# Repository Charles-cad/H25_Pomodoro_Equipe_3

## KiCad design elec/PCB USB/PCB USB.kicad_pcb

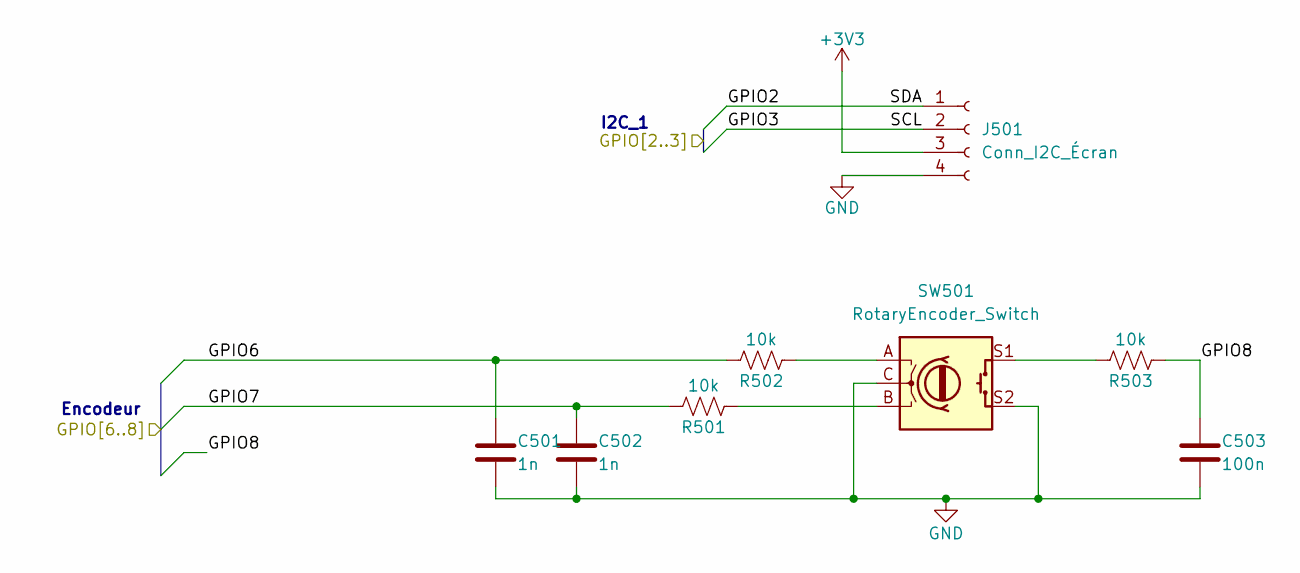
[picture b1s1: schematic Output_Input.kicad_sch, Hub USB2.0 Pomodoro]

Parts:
C501, C502: 1n; C_0603_1608Metric
C503: 100n; C_0603_1608Metric
J501: Conn_I2C_Écran; PinSocket_1x04_P2.54mm_Vertical
R501, R502, R503: 10k; R_0603_1608Metric
SW501: RotaryEncoder_Switch; RotaryEncoder_Bourns_Horizontal_PEC12R-2x17F-Sxxxx

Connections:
/MCU/GPIO6: C501.1, R502.1; also elsewhere on the board
/MCU/GPIO7: C502.1, R501.1; also elsewhere on the board
/MCU/GPIO8: C503.1, R503.2; also elsewhere on the board
unnamed: R501.2, SW501.B
unnamed: R502.2, SW501.A
unnamed: R503.1, SW501.S1

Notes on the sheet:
I2C_1
Encodeur

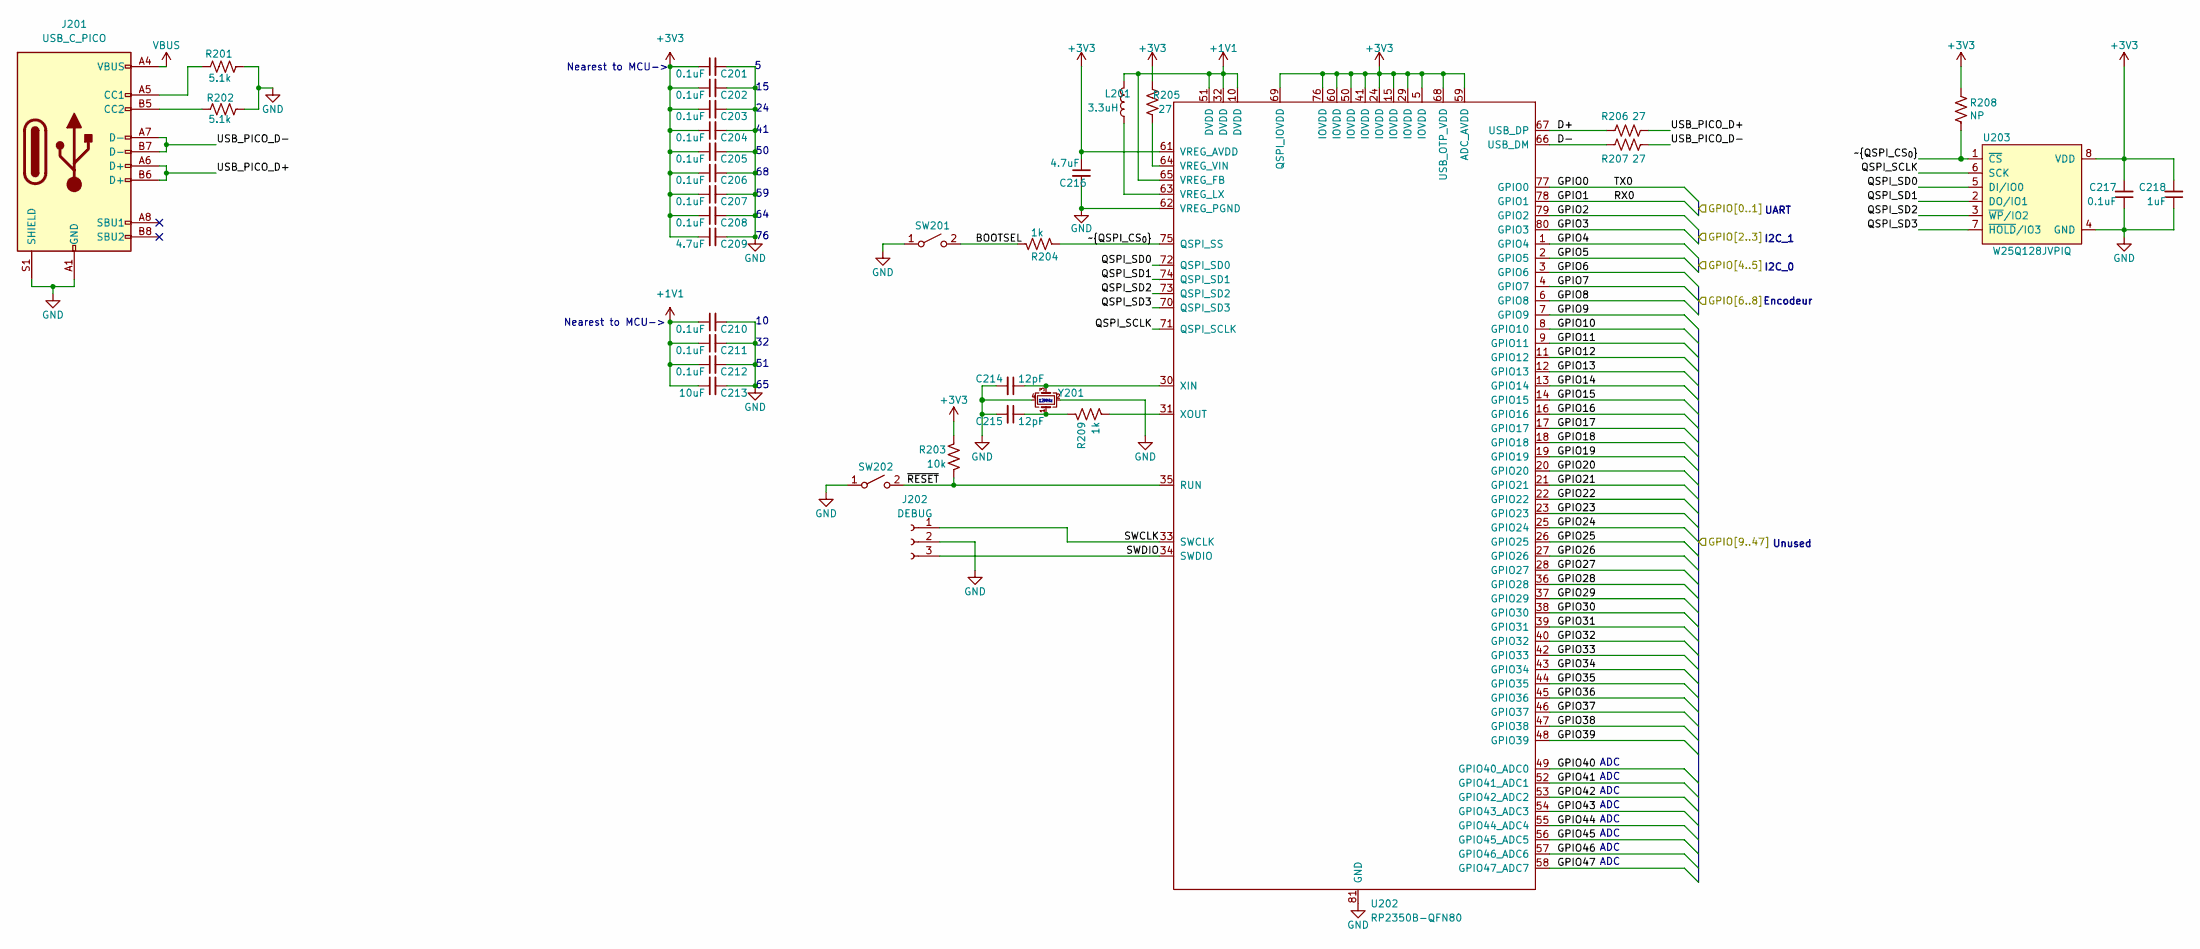
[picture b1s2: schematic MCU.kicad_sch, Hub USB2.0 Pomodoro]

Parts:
C201, C202, C203, C204, C205, C206, C207, C208, C210, C211, C212, C217: 0.1uF; C_0603_1608Metric
C209, C216: 4.7uF; C_0805_2012Metric
C213: 10uF; C_0805_2012Metric
C214, C215: 12pF; C_0603_1608Metric
C218: 1uF; C_0603_1608Metric
J201: USB_C_PICO; USB_C_Receptacle_G-Switch_GT-USB-7010ASV
J202: DEBUG; PinHeader_1x03_P2.54mm_Vertical
L201: 3.3uH; R_0805_2012Metric
R201, R202: 5.1k; R_0603_1608Metric_Pad0.98x0.95mm_HandSolder
R203: 10k; R_0603_1608Metric
R204, R209: 1k; R_0603_1608Metric
R205, R206, R207: 27; R_0603_1608Metric
R208: NP; R_0603_1608Metric
SW201: SW_BOOTSEL; SW_SPST_B3U-1000P; LCSC C561514
SW202: SW_RESET; SW_SPST_B3U-1000P; LCSC C561514
U202: RP2350B-QFN80; QFN-80-1EP_10x10mm_P0.4mm_EP3.4x3.4mm_ThermalVias
U203: W25Q128JVPIQ; WSON-8-1EP_6x5mm_P1.27mm_EP3.4x4mm; LCSC C190862
Y201: CM4012M00012001; Crystal_SMD_2520-4Pin_2.5x2.0mm; LCSC C7294611

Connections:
+1V1: C210.1, C211.1, C212.1, C213.1, L201.2, U202.10 (DVDD), U202.32 (DVDD), U202.51 (DVDD), U202.65 (VREG_FB)
+3V3: C201.1, C202.1, C203.1, C204.1, C205.1, C206.1, C207.1, C208.1, C209.1, C216.1, C217.2, C218.2, R203.1, R205.1, R208.2, U202.5 (IOVDD), U202.15 (IOVDD), U202.24 (IOVDD), U202.29 (IOVDD), U202.41 (IOVDD), U202.50 (IOVDD), U202.59 (ADC_AVDD), U202.60 (IOVDD), U202.61 (VREG_AVDD), U202.68 (USB_OTP_VDD), U202.69 (QSPI_IOVDD), U202.76 (IOVDD), U203.8 (VDD); also elsewhere on the board
/MCU/BOOTSEL: R204.2, SW201.2 (B)
/MCU/D+: R206.1, U202.67 (USB_DP)
/MCU/D-: R207.2, U202.66 (USB_DM)
/MCU/GPIO0: U202.77 (GPIO0)
/MCU/GPIO1: U202.78 (GPIO1)
/MCU/GPIO2: U202.79 (GPIO2); also elsewhere on the board
/MCU/GPIO3: U202.80 (GPIO3); also elsewhere on the board
/MCU/GPIO4: U202.1 (GPIO4)
/MCU/GPIO5: U202.2 (GPIO5)
/MCU/GPIO6: U202.3 (GPIO6); also elsewhere on the board
/MCU/GPIO7: U202.4 (GPIO7); also elsewhere on the board
/MCU/GPIO8: U202.6 (GPIO8); also elsewhere on the board
/MCU/GPIO9: U202.7 (GPIO9)
/MCU/GPIO10: U202.8 (GPIO10)
/MCU/GPIO11: U202.9 (GPIO11)
/MCU/GPIO12: U202.11 (GPIO12)
/MCU/GPIO13: U202.12 (GPIO13)
/MCU/GPIO14: U202.13 (GPIO14)
/MCU/GPIO15: U202.14 (GPIO15)
/MCU/GPIO16: U202.16 (GPIO16)
/MCU/GPIO17: U202.17 (GPIO17)
/MCU/GPIO18: U202.18 (GPIO18)
/MCU/GPIO19: U202.19 (GPIO19)
/MCU/GPIO20: U202.20 (GPIO20)
/MCU/GPIO21: U202.21 (GPIO21)
/MCU/GPIO22: U202.22 (GPIO22)
/MCU/GPIO23: U202.23 (GPIO23)
/MCU/GPIO24: U202.25 (GPIO24)
/MCU/GPIO25: U202.26 (GPIO25)
/MCU/GPIO26: U202.27 (GPIO26)
/MCU/GPIO27: U202.28 (GPIO27)
/MCU/GPIO28: U202.36 (GPIO28)
/MCU/GPIO29: U202.37 (GPIO29)
/MCU/GPIO30: U202.38 (GPIO30)
/MCU/GPIO31: U202.39 (GPIO31)
/MCU/GPIO32: U202.40 (GPIO32)
/MCU/GPIO33: U202.42 (GPIO33)
/MCU/GPIO34: U202.43 (GPIO34)
/MCU/GPIO35: U202.44 (GPIO35)
/MCU/GPIO36: U202.45 (GPIO36)
/MCU/GPIO37: U202.46 (GPIO37)
/MCU/GPIO38: U202.47 (GPIO38)
/MCU/GPIO39: U202.48 (GPIO39)
/MCU/GPIO40: U202.49 (GPIO40_ADC0)
/MCU/GPIO41: U202.52 (GPIO41_ADC1)
/MCU/GPIO42: U202.53 (GPIO42_ADC2)
/MCU/GPIO43: U202.54 (GPIO43_ADC3)
/MCU/GPIO44: U202.55 (GPIO44_ADC4)
/MCU/GPIO45: U202.56 (GPIO45_ADC5)
/MCU/GPIO46: U202.57 (GPIO46_ADC6)
/MCU/GPIO47: U202.58 (GPIO47_ADC7)
/MCU/QSPI_SCLK: U202.71 (QSPI_SCLK), U203.6 (SCK)
/MCU/QSPI_SD0: U202.72 (QSPI_SD0), U203.5 (DI/IO0)
/MCU/QSPI_SD1: U202.74 (QSPI_SD1), U203.2 (DO/IO1)
/MCU/QSPI_SD2: U202.73 (QSPI_SD2), U203.3 (~WP/IO2)
/MCU/QSPI_SD3: U202.70 (QSPI_SD3), U203.7 (~HOLD/IO3)
/MCU/SWCLK: J202.1, U202.33 (SWCLK); also elsewhere on the board
/MCU/SWDIO: J202.3, U202.34 (SWDIO); also elsewhere on the board
/MCU/USB_PICO_D+: J201.A6 (D+), J201.B6 (D+), R206.2
/MCU/USB_PICO_D-: J201.A7 (D-), J201.B7 (D-), R207.1
/MCU/~QSPI_CS_{0}: R204.1, R208.1, U202.75 (QSPI_SS), U203.1 (~CS)
/MCU/~RESET: R203.2, SW202.2 (B), U202.35 (RUN)
unnamed: C215.1, R209.1, Y201.1
unnamed: J201.A5 (CC1), R201.1
unnamed: J201.B5 (CC2), R202.1
unnamed: L201.1, U202.63 (VREG_LX)
unnamed: R205.2, U202.64 (VREG_VIN)
unnamed: C214.1, U202.30 (XIN), Y201.3
unnamed: R209.2, U202.31 (XOUT)
VBUS: J201.A4 (VBUS), J201.A9 (VBUS), J201.B4 (VBUS), J201.B9 (VBUS); also elsewhere on the board

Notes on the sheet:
Encodeur
Nearest to MCU->
UART
I2C_0
ADC
I2C_1
12MHz
Unused

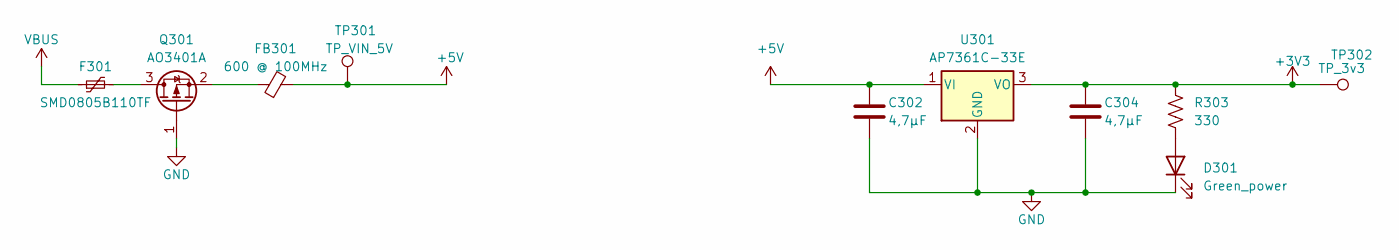
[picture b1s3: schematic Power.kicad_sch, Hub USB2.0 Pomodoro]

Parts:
C302, C304: 4,7µF; C_0805_2012Metric_Pad1.18x1.45mm_HandSolder
D301: Green_power; D_0805_2012Metric
F301: SMD0805B110TF; Fuse_0805_2012Metric
FB301: 600 @ 100MHz; R_0805_2012Metric_Pad1.20x1.40mm_HandSolder
Q301: AO3401A; SOT-23
R303: 330; R_0603_1608Metric_Pad0.98x0.95mm_HandSolder
TP301: TP_VIN_5V; TestPoint_Pad_D1.0mm
TP302: TP_3v3; TestPoint_Pad_D1.0mm
U301: AP7361C-33E; SOT-223-3_TabPin2

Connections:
+3V3: C304.2, R303.1, TP302.1, U301.3 (VO); also elsewhere on the board
+5V: C302.2, FB301.2, TP301.1, U301.1 (VI); also elsewhere on the board
unnamed: D301.2 (A), R303.2
unnamed: F301.2, Q301.3 (D)
unnamed: FB301.1, Q301.2 (S)
VBUS: F301.1; also elsewhere on the board

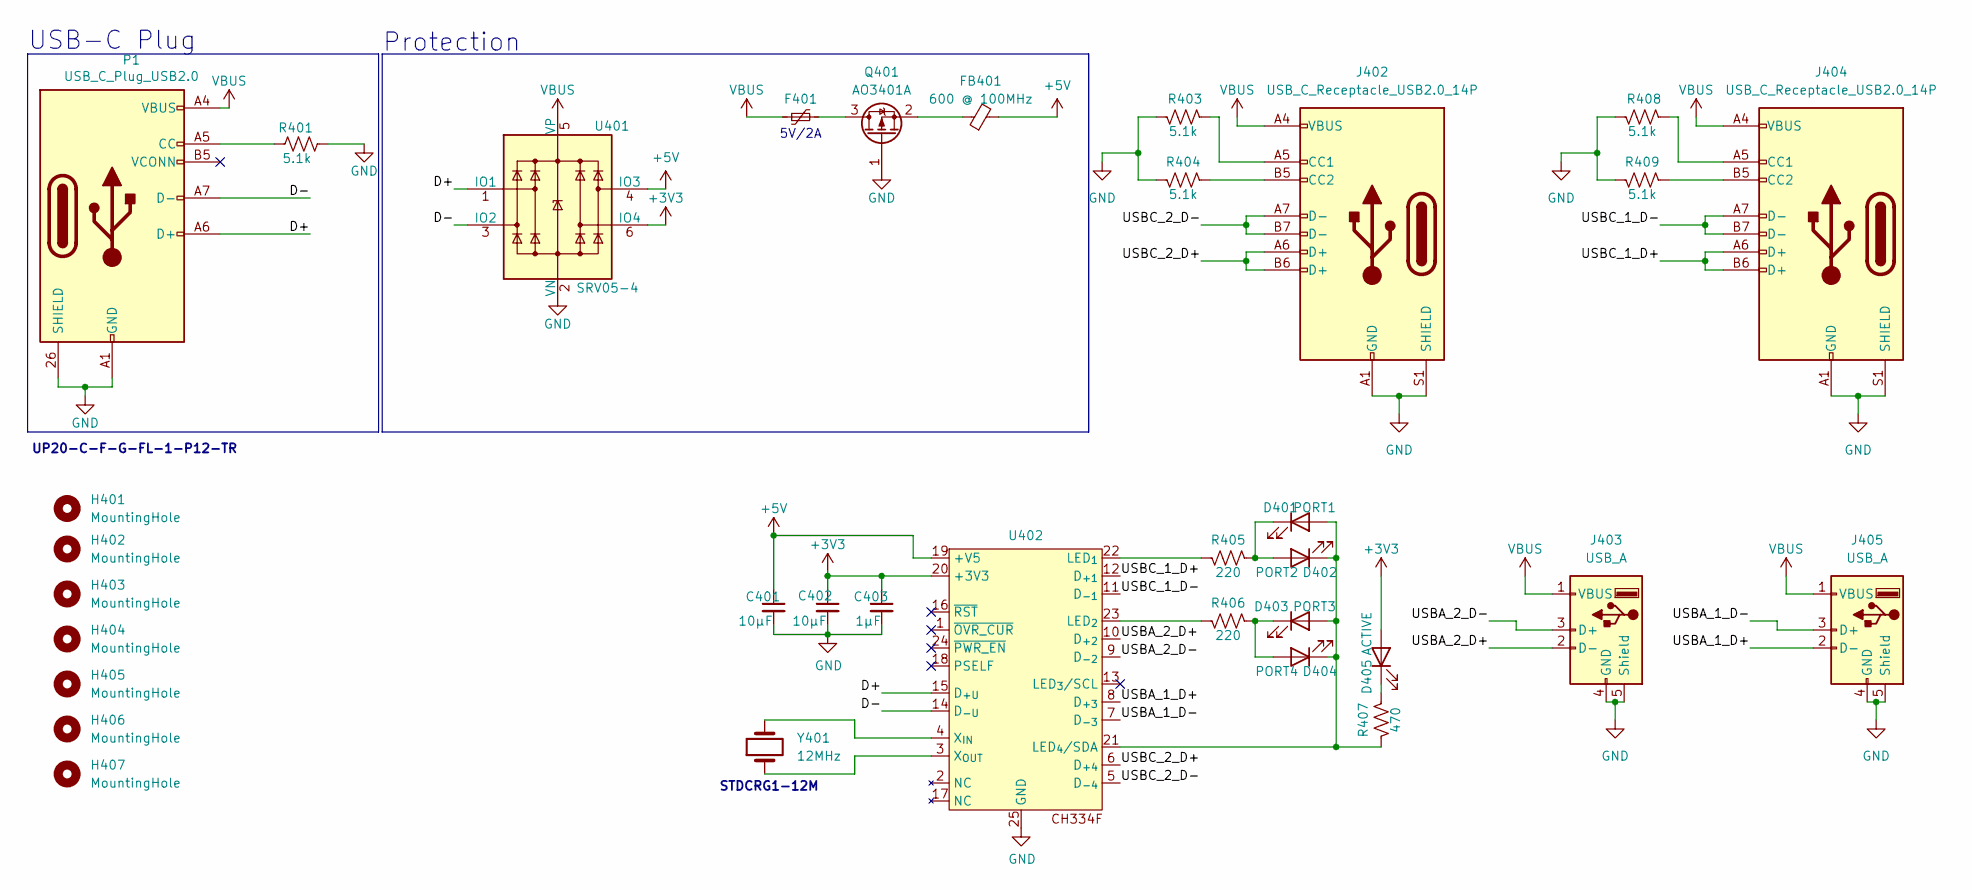
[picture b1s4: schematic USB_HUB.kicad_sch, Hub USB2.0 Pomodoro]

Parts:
C401, C402: 10µF; C_0805_2012Metric
C403: 1µF; C_0603_1608Metric
D401: PORT1; D_0805_2012Metric
D402: PORT2; D_0805_2012Metric
D403: PORT3; D_0805_2012Metric
D404: PORT4; D_0805_2012Metric
D405: ACTIVE; D_0805_2012Metric
F401: SMD0805B110TF; Fuse_0805_2012Metric
FB401: 600 @ 100MHz; R_0805_2012Metric_Pad1.20x1.40mm_HandSolder
H401, H402, H403, H404, H405, H406, H407: MountingHole; MountingHole_2.2mm_M2
J402, J404: USB_C_Receptacle_USB2.0_14P; USB_C_Receptacle_G-Switch_GT-USB-7010ASV
J403, J405: USB_A; USB_A_CONNFLY_DS1095-WNR0
P1: USB_C_Plug_USB2.0; UP20-C-F-G-FL-1-P12-TR; MPN C2856663
Q401: AO3401A; SOT-23
R401: 5.1k; R_0603_1608Metric_Pad0.98x0.95mm_HandSolder
R403, R404, R408, R409: 5.1k; R_0603_1608Metric
R405, R406: 220; R_0603_1608Metric
R407: 470; R_0603_1608Metric
U401: SRV05-4; SOT-23-6
U402: HVQFN-24-1EP_4x4mm_P0.5mm_EP2.6x2.6mm
Y401: 12MHz; Crystal_SMD_3225-4Pin_3.2x2.5mm

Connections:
+3V3: C402.1, C403.1, D405.2 (A), U401.6 (IO4), U402.20 (+3V3); also elsewhere on the board
+5V: C401.1, FB401.2, U401.4 (IO3), U402.19 (+V5); also elsewhere on the board
/USB_HUB/D+: P1.A6 (D+), U401.1 (IO1), U402.15 (D_{+U})
/USB_HUB/D-: P1.A7 (D-), U401.3 (IO2), U402.14 (D_{-U})
/USB_HUB/USBA_1_D+: J405.2 (D-), U402.8 (D_{+3})
/USB_HUB/USBA_1_D-: J405.3 (D+), U402.7 (D_{-3})
/USB_HUB/USBA_2_D+: J403.2 (D-), U402.10 (D_{+2})
/USB_HUB/USBA_2_D-: J403.3 (D+), U402.9 (D_{-2})
/USB_HUB/USBC_1_D+: J404.A6 (D+), J404.B6 (D+), U402.12 (D_{+1})
/USB_HUB/USBC_1_D-: J404.A7 (D-), J404.B7 (D-), U402.11 (D_{-1})
/USB_HUB/USBC_2_D+: J402.A6 (D+), J402.B6 (D+), U402.6 (D_{+4})
/USB_HUB/USBC_2_D-: J402.A7 (D-), J402.B7 (D-), U402.5 (D_{-4})
unnamed: D401.2 (A), D402.1 (K), D403.2 (A), D404.1 (K), R407.2, U402.21 (LED_{4}/SDA)
unnamed: D401.1 (K), D402.2 (A), R405.1
unnamed: D403.1 (K), D404.2 (A), R406.1
unnamed: D405.1 (K), R407.1
unnamed: J402.A5 (CC1), R403.1
unnamed: J402.B5 (CC2), R404.1
unnamed: J404.A5 (CC1), R408.1
unnamed: J404.B5 (CC2), R409.1
unnamed: P1.A5 (CC), R401.1
unnamed: F401.2, Q401.3 (D)
unnamed: FB401.1, Q401.2 (S)
unnamed: R405.2, U402.22 (LED_{1})
unnamed: R406.2, U402.23 (LED_{2})
unnamed: U402.3 (X_{OUT}), Y401.1
VBUS: F401.1, J402.A4 (VBUS), J402.A9 (VBUS), J402.B4 (VBUS), J402.B9 (VBUS), J403.1 (VBUS), J404.A4 (VBUS), J404.A9 (VBUS), J404.B4 (VBUS), J404.B9 (VBUS), J405.1 (VBUS), P1.A4 (VBUS), P1.A9 (VBUS), P1.B4 (VBUS), P1.B9 (VBUS), U401.5 (VP); also elsewhere on the board

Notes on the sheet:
STDCRG1-12M
Protection
UP20-C-F-G-FL-1-P12-TR
5V/2A
USB-C Plug

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
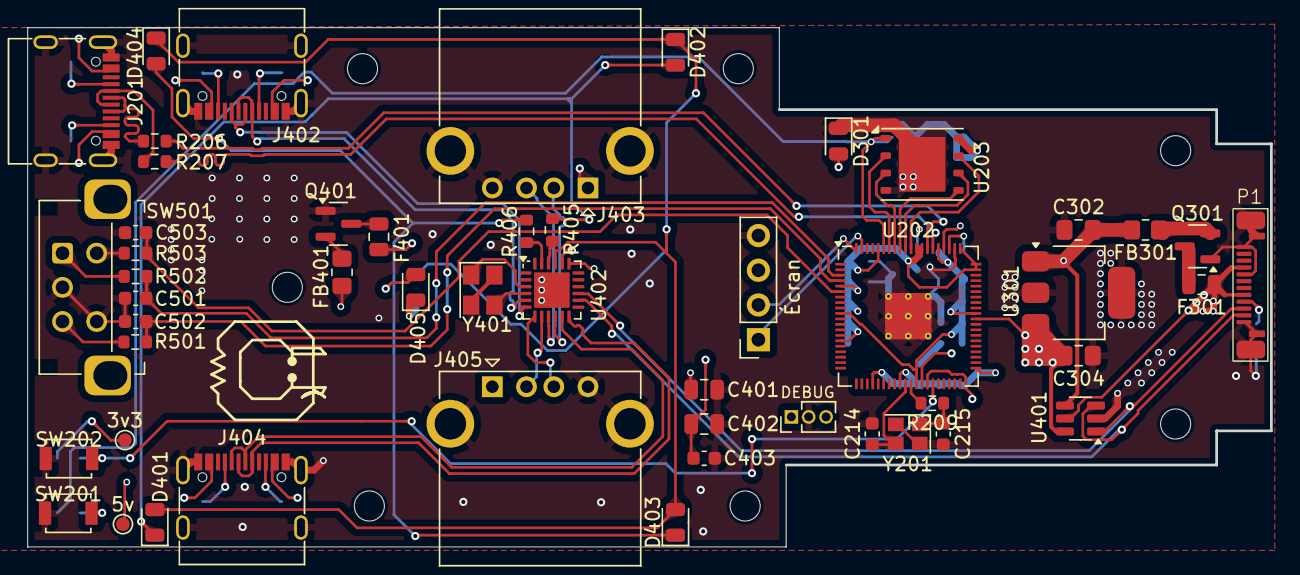
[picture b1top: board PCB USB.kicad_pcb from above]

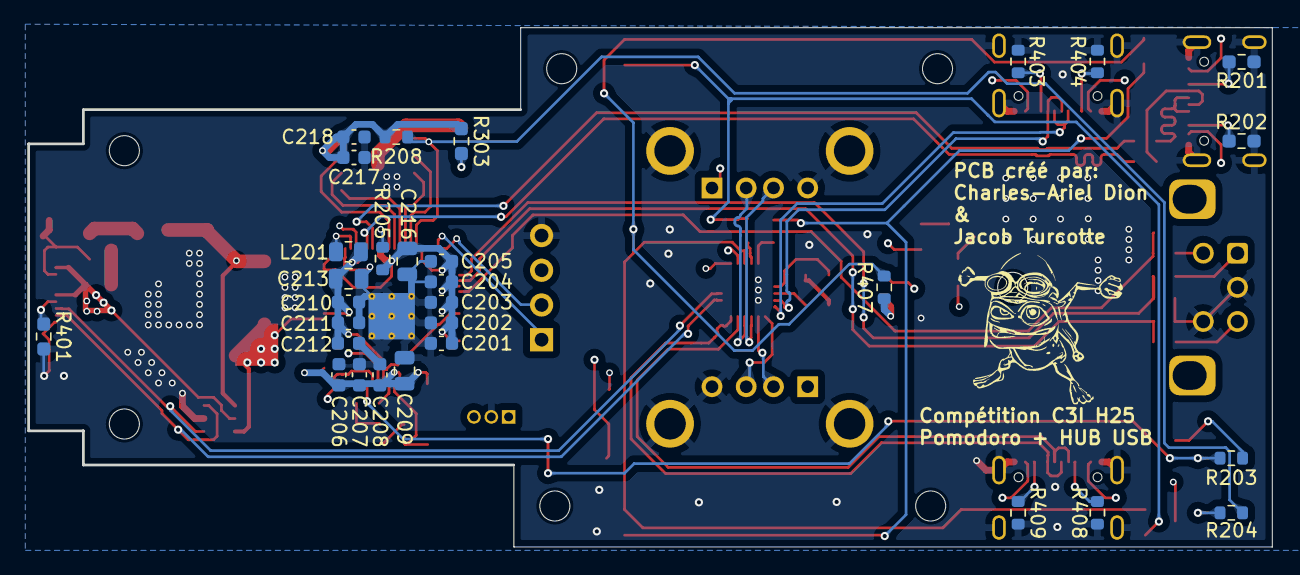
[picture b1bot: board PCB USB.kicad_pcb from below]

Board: 4 copper layers, 90.9 x 37.9 mm, 87 parts (30 on the bottom side), 62 nets.

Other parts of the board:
3v3: TP_3v3; TestPoint_Pad_D1.0mm
5v: TP_VIN_5V; TestPoint_Pad_D1.0mm
DEBUG: DEBUG; PinHeader_1x03_P1.27mm_Vertical
Écran: Conn_I2C_Écran; PinSocket_1x04_P2.54mm_Vertical

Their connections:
+3V3: 3v3.1, Écran.3; also elsewhere on the board
+5V: 5v.1; also elsewhere on the board
/MCU/GPIO2: Écran.1; also elsewhere on the board
/MCU/GPIO3: Écran.2; also elsewhere on the board
/MCU/SWCLK: DEBUG.1; also elsewhere on the board
/MCU/SWDIO: DEBUG.3; also elsewhere on the board

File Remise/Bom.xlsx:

Reference | Qty | Value | Footprint | Distributeur | Prix
C201,C202,C203,C204,C205,C206,C207,C208,C210,C211,C212,C217 | 12 | 0.1uF | Capacitor_SMD:C_0603_1608Metric | lcsc | 1.6000000000000001E-3
C209,C216 | 2 | 4.7uF | Capacitor_SMD:C_0805_2012Metric | lcsc | 4.1999999999999997E-3
C213 | 1 | 10uF | Capacitor_SMD:C_0805_2012Metric | lcsc | 6.1999999999999998E-3
C214,C215 | 2 | 10pF | Capacitor_SMD:C_0603_1608Metric | Digikey | 3.5999999999999997E-2
C218 | 1 | 1uF | Capacitor_SMD:C_0603_1608Metric | lcsc | 6.6E-3
C302,C304 | 2 | 4,7µF | Capacitor_SMD:C_0805_2012Metric_Pad1.18x1.45mm_HandSolder | lcsc | 4.1999999999999997E-3
C401,C402 | 2 | 10µF | Capacitor_SMD:C_0805_2012Metric | lcsc | 6.1999999999999998E-3
C403 | 1 | 1µF | Capacitor_SMD:C_0603_1608Metric | lcsc | 6.6E-3
C501,C502 | 2 | 1n | Capacitor_SMD:C_0603_1608Metric | lcsc | 1.6999999999999999E-3
C503 | 1 | 100n | Capacitor_SMD:C_0603_1608Metric | lcsc | 1.6000000000000001E-3
D301 | 1 | Green_power | Diode_SMD:D_0805_2012Metric | lcsc | 7.2999999999999995E-2
D401 | 1 | PORT1 | Diode_SMD:D_0805_2012Metric | lcsc | 7.2999999999999995E-2
D402 | 1 | PORT2 | Diode_SMD:D_0805_2012Metric | lcsc | 7.2999999999999995E-2
D403 | 1 | PORT3 | Diode_SMD:D_0805_2012Metric | lcsc | 7.2999999999999995E-2
D404 | 1 | PORT4 | Diode_SMD:D_0805_2012Metric | lcsc | 7.2999999999999995E-2
D405 | 1 | ACTIVE | Diode_SMD:D_0805_2012Metric | Digikey | 7.2999999999999995E-2
F301,F401 | 2 | SMD0805B110TF | Fuse:Fuse_0805_2012Metric | Digikey | 0.19
FB301,FB401 | 2 | 600 @ 100MHz | Resistor_SMD:R_0805_2012Metric_Pad1.20x1.40mm_HandSolder | Digikey | 0.6
J201 | 1 | USB_C_PICO | Connector_USB:USB_C_Receptacle_G-Switch_GT-USB-7010ASV | lcsc | 6.1600000000000002E-2
J202 | 1 | DEBUG | Connector_PinHeader_2.54mm:PinHeader_1x03_P2.54mm_Vertical | - | 0
J402,J404 | 2 | USB_C_Receptacle_USB2.0_14P | Connector_USB:USB_C_Receptacle_G-Switch_GT-USB-7010ASV | lcsc | 6.1600000000000002E-2
J403,J405 | 2 | USB_A | Connector_USB:USB_A_CONNFLY_DS1095-WNR0 | Amazon | 3.4700000000000002E-2
J501 | 1 | Conn_I2C_Écran | Connector_PinSocket_2.54mm:PinSocket_1x04_P2.54mm_Vertical | - | 5.33
L201 | 1 | 3.3uH | Resistor_SMD:R_0805_2012Metric | Digikey | 0.15
P1 | 1 | USB_C_Plug_USB2.0 | JT_USB_C:UP20-C-F-G-FL-1-P12-TR | lcsc | 6.1600000000000002E-2
Q301,Q401 | 2 | AO3401A | Package_TO_SOT_SMD:SOT-23 | Digikey | 0.7
R201,R202,R401 | 3 | 5.1k | Resistor_SMD:R_0603_1608Metric_Pad0.98x0.95mm_HandSolder | Digikey | 1.4999999999999999E-2
R203,R501,R502,R503 | 4 | 10k | Resistor_SMD:R_0603_1608Metric | lcsc | 8.0000000000000004E-4
R204,R209 | 2 | 1k | Resistor_SMD:R_0603_1608Metric | lcsc | 1E-3
R205,R206,R207 | 3 | 27 | Resistor_SMD:R_0603_1608Metric | Digikey | 1.2999999999999999E-2
R208 | 1 | NP | Resistor_SMD:R_0603_1608Metric | - | 0
R303 | 1 | 330 | Resistor_SMD:R_0603_1608Metric_Pad0.98x0.95mm_HandSolder | lcsc | 8.0000000000000004E-4
R403,R404,R408,R409 | 4 | 5.1k | Resistor_SMD:R_0603_1608Metric | Digikey | 1.4999999999999999E-2
R405,R406 | 2 | 220 | Resistor_SMD:R_0603_1608Metric | lcsc | 8.9999999999999998E-4
R407 | 1 | 470 | Resistor_SMD:R_0603_1608Metric | lcsc | 6.9999999999999999E-4
SW201 | 1 | SW_BOOTSEL | Button_Switch_SMD:SW_SPST_B3U-1000P | lcsc | 7.2900000000000006E-2
SW202 | 1 | SW_RESET | Button_Switch_SMD:SW_SPST_B3U-1000P | lcsc | 7.2900000000000006E-2
SW501 | 1 | RotaryEncoder_Switch | Rotary_Encoder:RotaryEncoder_Bourns_Horizontal_PEC12R-2x17F-Sxxxx | Digikey | 2.66
U202 | 1 | RP2350B-QFN80 | Package_DFN_QFN:QFN-80-1EP_10x10mm_P0.4mm_EP3.4x3.4mm_ThermalVias | Aliexpress | 3.76
U203 | 1 | W25Q128JVPIQ | Package_SON:WSON-8-1EP_6x5mm_P1.27mm_EP3.4x4mm | Digikey | 1.92
U301 | 1 | AP7361C-33E | Package_TO_SOT_SMD:SOT-223-3_TabPin2 | Digikey | 1.56
U401 | 1 | SRV05-4 | Package_TO_SOT_SMD:SOT-23-6 | Digikey | 0.108
U402 | 1 | CH334F | Package_DFN_QFN:HVQFN-24-1EP_4x4mm_P0.5mm_EP2.6x2.6mm | lcsc | 0.55000000000000004
Y201 | 1 | CM4012M00012001 | Crystal:Crystal_SMD_2520-4Pin_2.5x2.0mm | Digikey | 0.34
Y401 | 1 | 12MHz | Crystal:Crystal_SMD_3225-4Pin_3.2x2.5mm | Digikey | 0.28999999999999998
 |  |  |  | Total: | 20.844900000000003
 |  |  |  |  | 4
 |  |  |  |  | 24.844900000000003

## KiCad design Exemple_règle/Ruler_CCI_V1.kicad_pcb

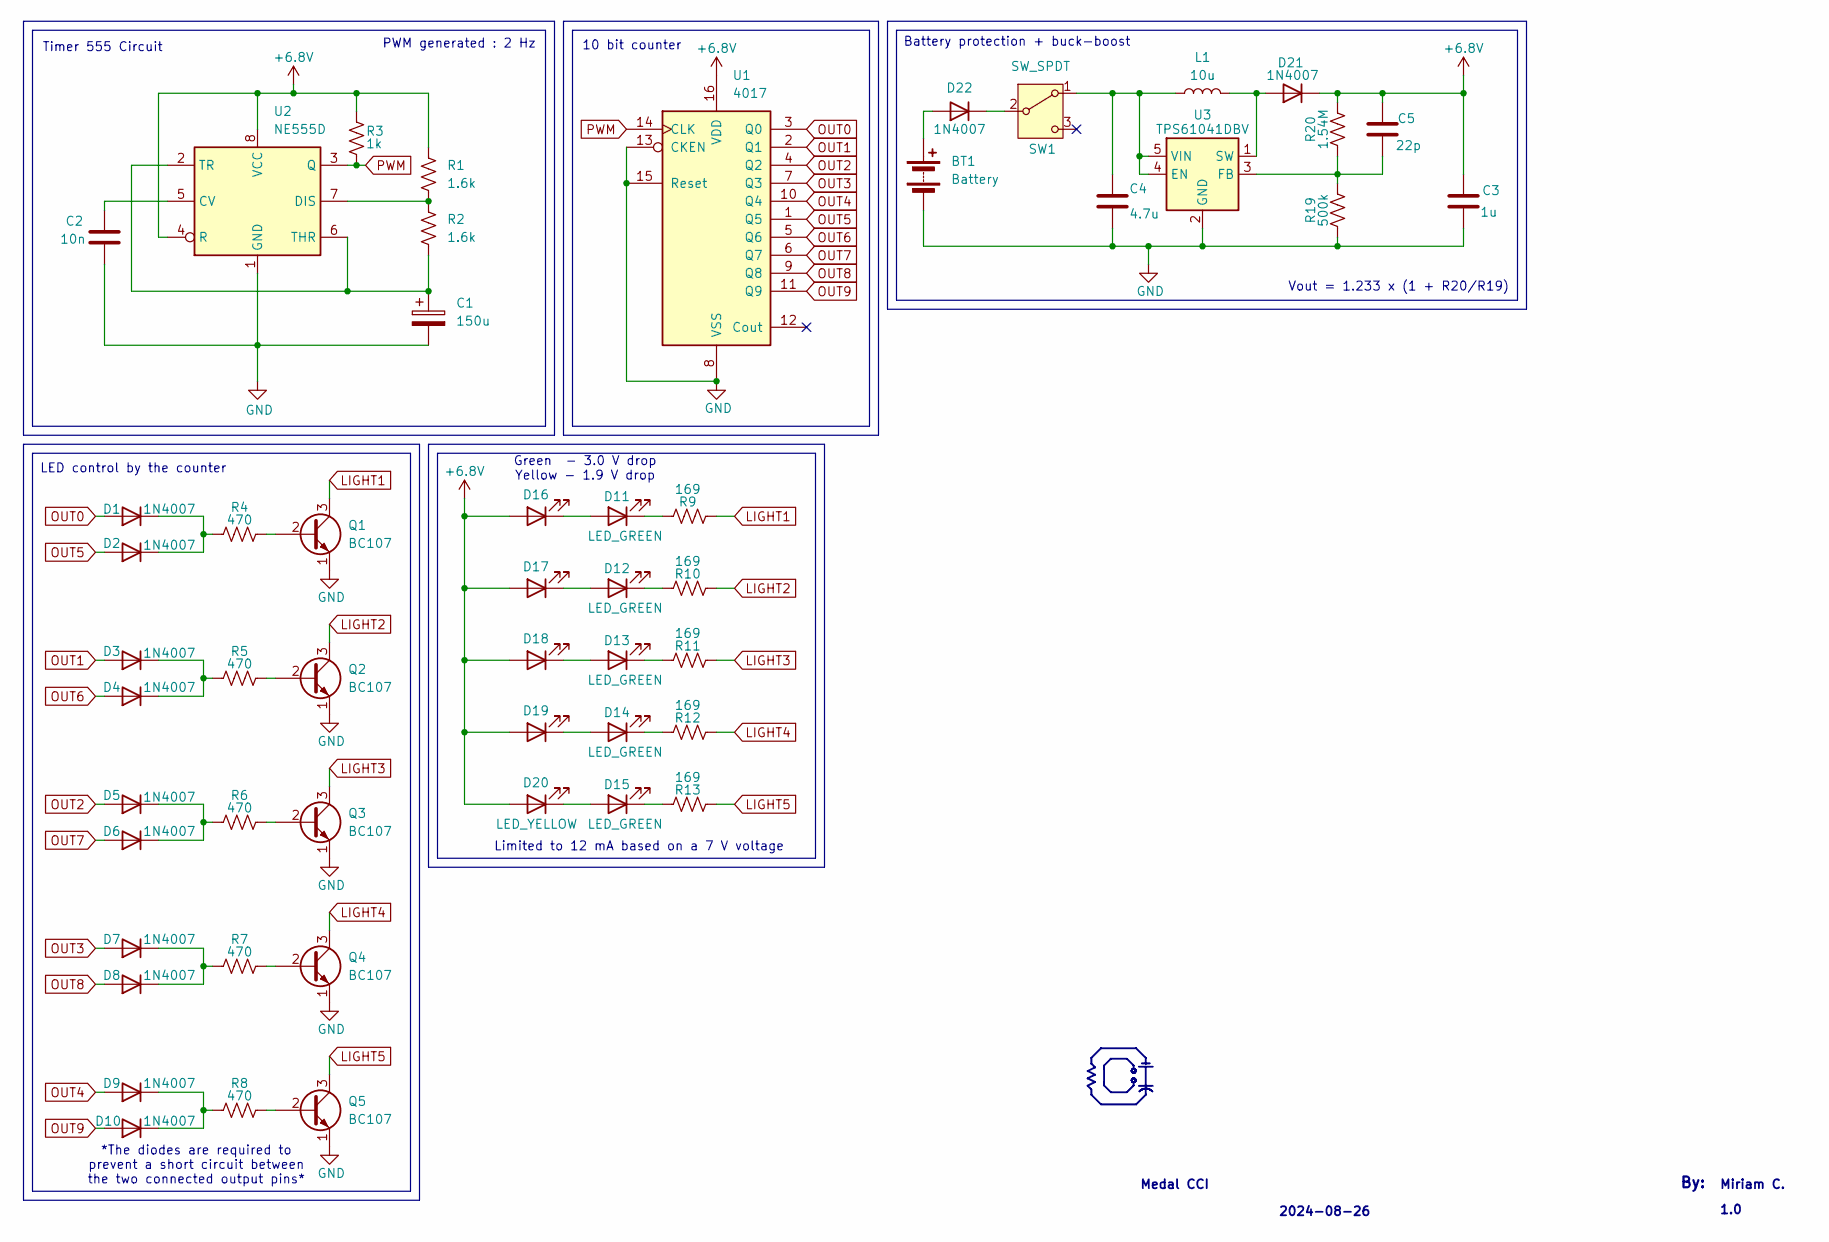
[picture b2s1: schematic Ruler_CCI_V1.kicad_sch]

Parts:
BT1: Battery; BAT_SMD_CR1220
C1: 150u; CP_Elec_6.3x7.7
C2: 10n; C_0603_1608Metric
C3: 1u; L_0603_1608Metric_Pad1.05x0.95mm_HandSolder
C4: 4.7u; L_0603_1608Metric_Pad1.05x0.95mm_HandSolder
C5: 22p; L_0603_1608Metric_Pad1.05x0.95mm_HandSolder
D1, D2, D3, D4, D5, D6, D7, D8, D9, D10, D21, D22: 1N4007; D_SOD-123F
D11, D12, D13, D14, D15: LED_GREEN; D_0603_1608Metric_Pad1.05x0.95mm_HandSolder
D16, D17, D18, D19, D20: LED_YELLOW; D_0603_1608Metric_Pad1.05x0.95mm_HandSolder
L1: 10u; L_0805_2012Metric_Pad1.15x1.40mm_HandSolder
Q1, Q2, Q3, Q4, Q5: BC107; SOT-23
R1, R2: 1.6k; R_0603_1608Metric_Pad0.98x0.95mm_HandSolder
R3: 1k; R_0603_1608Metric_Pad0.98x0.95mm_HandSolder
R4, R5, R6, R7, R8: 470; R_0603_1608Metric_Pad0.98x0.95mm_HandSolder
R9, R10, R11, R12, R13: 169; R_0603_1608Metric_Pad0.98x0.95mm_HandSolder
R19: 500k; R_0603_1608Metric_Pad0.98x0.95mm_HandSolder
R20: 1.54M; R_0603_1608Metric_Pad0.98x0.95mm_HandSolder
SW1: SW_SPDT; SW_SPDT_PCM12
U1: 4017; SOP-16_3.9x9.9mm_P1.27mm
U2: NE555D; SOIC-8_3.9x4.9mm_P1.27mm
U3: TPS61041DBV; SOT-23-5

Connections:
+6.8V: C3.1, C5.1, D16.2 (A), D17.2 (A), D18.2 (A), D19.2 (A), D20.2 (A), D21.1 (K), R1.1, R3.1, R20.2, U1.16 (VDD), U2.4 (R), U2.8 (VCC)
GND: BT1.2 (-), C1.2, C2.2, C3.2, C4.2, Q1.1 (E), Q2.1 (E), Q3.1 (E), Q4.1 (E), Q5.1 (E), R19.1, U1.8 (VSS), U1.13 (CKEN), U1.15 (Reset), U2.1 (GND), U3.2 (GND)
LIGHT1: Q1.3 (C), R9.1
LIGHT2: Q2.3 (C), R10.1
LIGHT3: Q3.3 (C), R11.1
LIGHT4: Q4.3 (C), R12.1
LIGHT5: Q5.3 (C), R13.1
unnamed: BT1.1 (+), D22.2 (A)
unnamed: D1.1 (K), D2.1 (K), R4.1
unnamed: D3.1 (K), D4.1 (K), R5.1
unnamed: D5.1 (K), D6.1 (K), R6.1
unnamed: D7.1 (K), D8.1 (K), R7.1
unnamed: D9.1 (K), D10.1 (K), R8.1
unnamed: D11.2 (A), D16.1 (K)
unnamed: D11.1 (K), R9.2
unnamed: D12.2 (A), D17.1 (K)
unnamed: D12.1 (K), R10.2
unnamed: D13.2 (A), D18.1 (K)
unnamed: D13.1 (K), R11.2
unnamed: D14.2 (A), D19.1 (K)
unnamed: D14.1 (K), R12.2
unnamed: D15.2 (A), D20.1 (K)
unnamed: D15.1 (K), R13.2
unnamed: D21.2 (A), L1.2, U3.1 (SW)
unnamed: D22.1 (K), SW1.2 (B)
unnamed: Q1.2 (B), R4.2
unnamed: Q2.2 (B), R5.2
unnamed: Q3.2 (B), R6.2
unnamed: Q4.2 (B), R7.2
unnamed: Q5.2 (B), R8.2
unnamed: C4.1, L1.1, SW1.1 (A), U3.4 (EN), U3.5 (VIN)
unnamed: C2.1, U2.5 (CV)
unnamed: R1.2, R2.1, U2.7 (DIS)
unnamed: C1.1, R2.2, U2.2 (TR), U2.6 (THR)
unnamed: C5.2, R19.2, R20.1, U3.3 (FB)
OUT0: D1.2 (A), U1.3 (Q0)
OUT1: D3.2 (A), U1.2 (Q1)
OUT2: D5.2 (A), U1.4 (Q2)
OUT3: D7.2 (A), U1.7 (Q3)
OUT4: D9.2 (A), U1.10 (Q4)
OUT5: D2.2 (A), U1.1 (Q5)
OUT6: D4.2 (A), U1.5 (Q6)
OUT7: D6.2 (A), U1.6 (Q7)
OUT8: D8.2 (A), U1.9 (Q8)
OUT9: D10.2 (A), U1.11 (Q9)
PWM: R3.2, U1.14 (CLK), U2.3 (Q)

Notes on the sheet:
Miriam C.
10 bit counter
2024-08-26
Limited to 12 mA based on a 7 V voltage
LED control by the counter
Green - 3.0 V drop Yellow - 1.9 V drop
By:
1.0
Battery protection + buck-boost
PWM generated : 2 Hz
Timer 555 Circuit
*The diodes are required to prevent a short circuit between the two connected output pins*
Vout = 1.233 x (1 + R20/R19)
Medal CCI

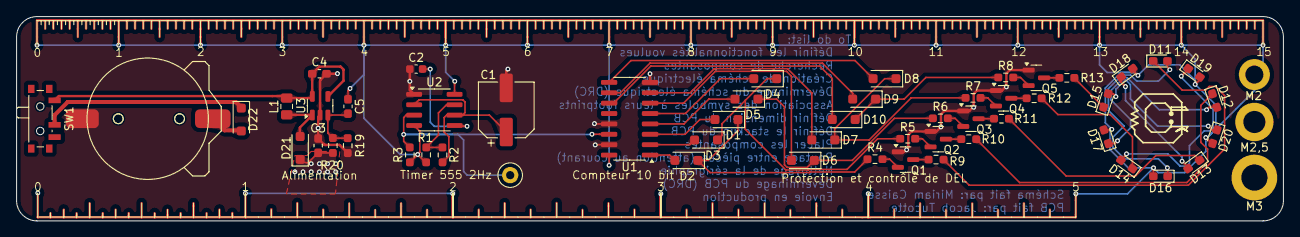
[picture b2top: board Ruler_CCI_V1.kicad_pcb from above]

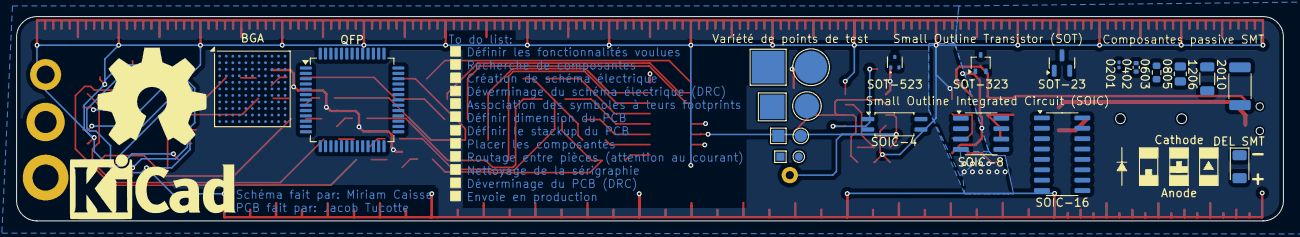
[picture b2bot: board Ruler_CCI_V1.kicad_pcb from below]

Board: 2 copper layers, 155.0 x 25.0 mm, 71 parts (15 on the bottom side), 46 nets.

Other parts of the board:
0201: R_0201_0603Metric
0402: R_0402_1005Metric
0603: R_0603_1608Metric
0805: R_0805_2012Metric
1206: R_1206_3216Metric
2010: R_2010_5025Metric
BGA: BGA-121_9.0x9.0mm_Layout11x11_P0.8mm_Ball0.4mm_Pa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; BGA-121_9.0x9.0mm_Layout11x11_P0.8mm_Ball0.4mm_Pad0.35mm_NS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
DEL SMT: LED_1206_3216Metric
M2: MountingHole_2.2mm_M2_DIN965_Pad
M2,5: MountingHole_2.7mm_M2.5_DIN965_Pad
M3: MountingHole_3.2mm_M3_DIN965_Pad
QFP: LQFP-52_10x10mm_P0.65mm
SOIC-4: SOIC-4_4.55x2.6mm_P1.27mm
SOIC-8: SOIC-8_3.9x4.9mm_P1.27mm
SOIC-16: SOIC-16_3.9x9.9mm_P1.27mm
SOT-23: SOT-23
SOT-323: SOT-323_SC-70
SOT-523: SOT-523

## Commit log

2025-03-10 projet
2025-03-10 creation projet vide
2025-03-10 debut du projet avec dimensions dans le PCB
2025-03-10 Ajout des USB A et C
2025-03-10 push rp2350, USB hub, power. SCHEMATIC
2025-03-11 push schema
2025-03-11 push sélection pièces et schéma électrique clean up
2025-03-11 PUSHHHHHHHHHHHH
2025-03-11 placements trucs usb
2025-03-11 speed
2025-03-11 All components placed (no traces yet tho)
2025-03-11 push pcb
2025-03-11 oh shit game de volley
2025-03-12 push finalisation pcb et silkscreen
2025-03-12 tear drops
2025-03-12 push crystal fix
2025-04-01 push kicad fix
2025-04-01 push step
2025-04-19 backup push
2025-04-19 Classe de screen et boutton fonctionnel
2025-04-19 Pomodoro v1
    bare minimum is fonctionnal:)
    would be nice to add logos and stuff
2025-04-20 Push pour remise
2025-04-21 Push non terminé
2025-04-21 push doc
2025-04-27 push encoder button task manager
2025-04-27 push code orientation fix
2025-04-30 push???
